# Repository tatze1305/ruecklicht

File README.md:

# Project Title

Look in PDF/schematic and PDF/pcb!!!

---

## 3D Preview

### Rücklicht – Back View

### Rücklicht – Front View

---

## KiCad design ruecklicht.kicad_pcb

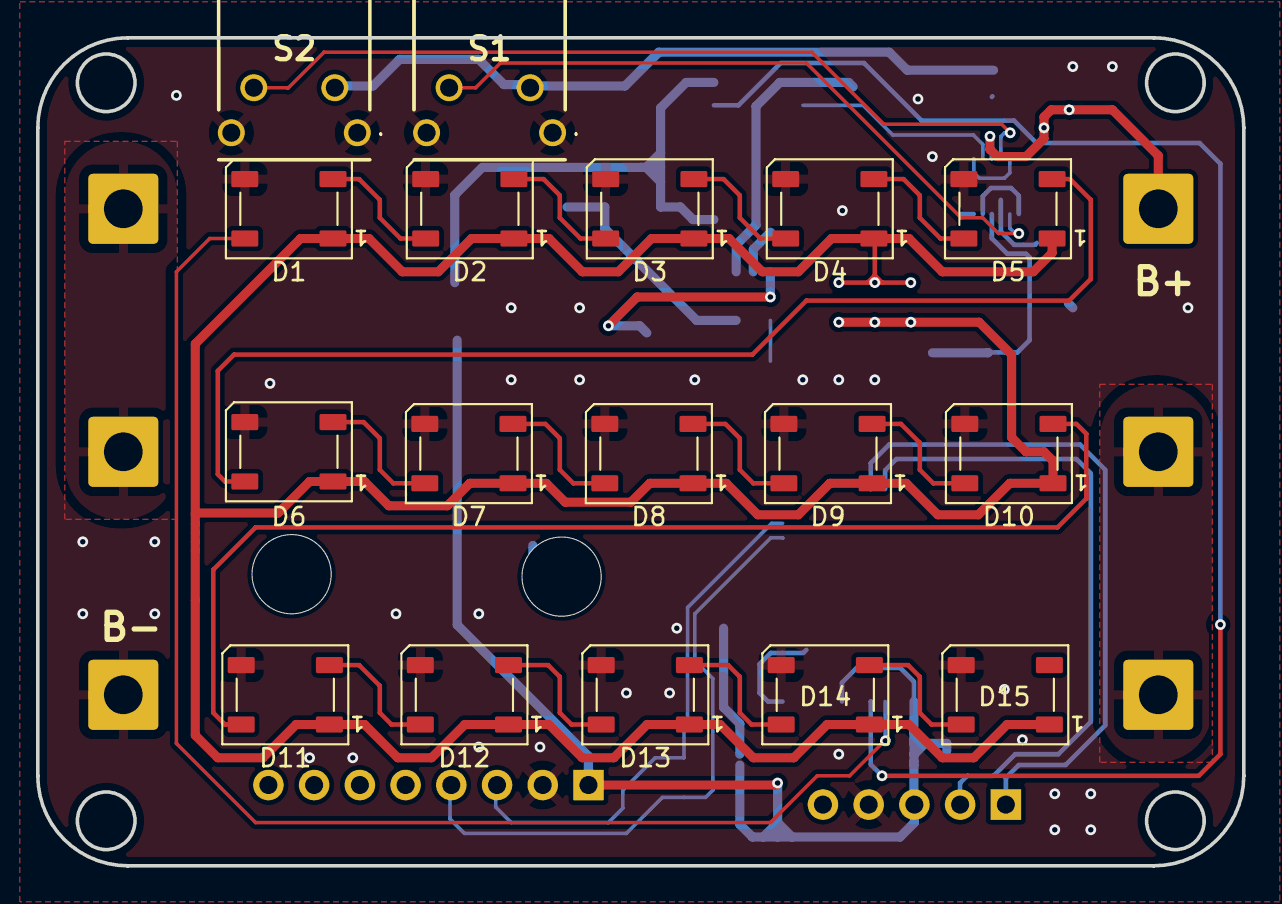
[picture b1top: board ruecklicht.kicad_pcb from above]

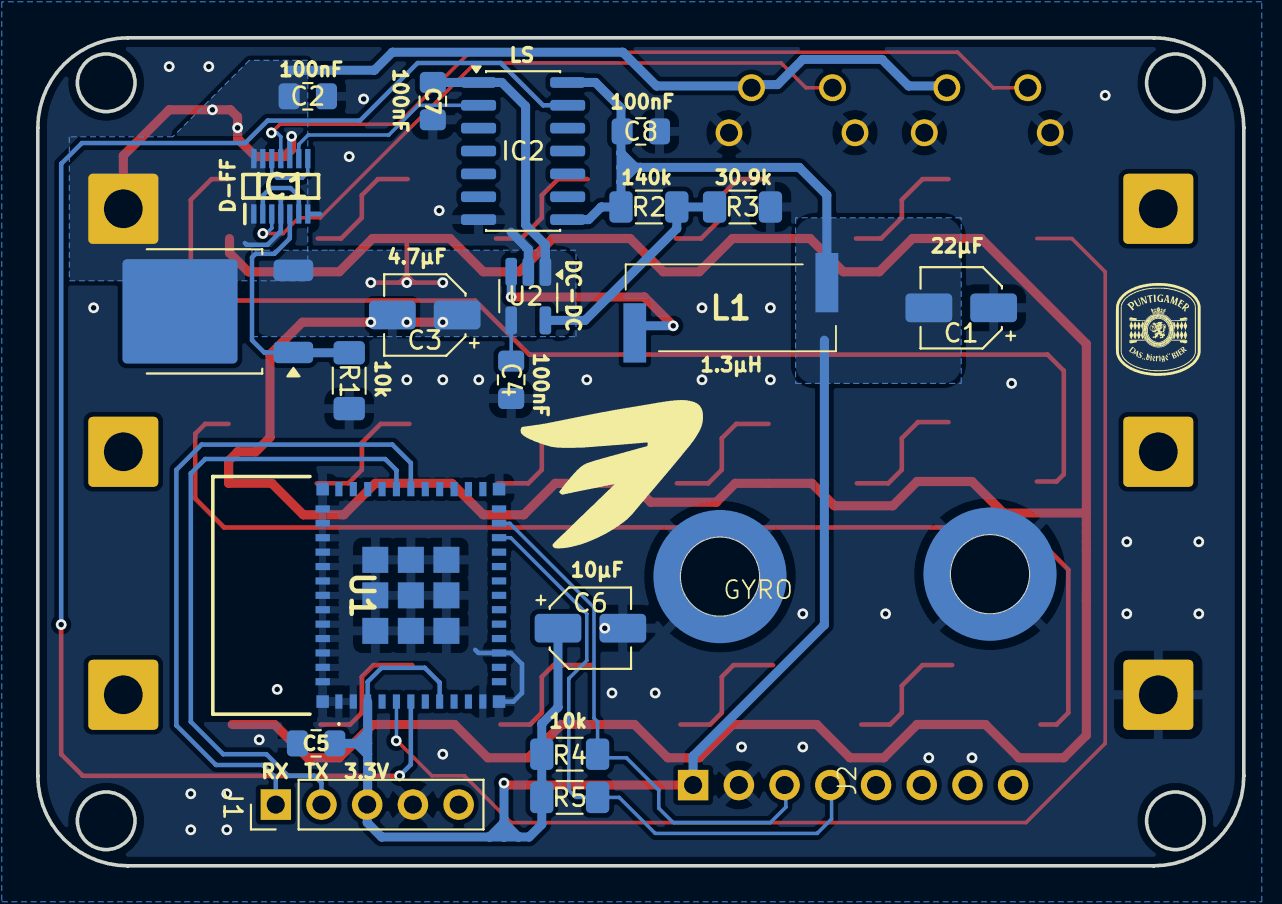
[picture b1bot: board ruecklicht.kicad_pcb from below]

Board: 2 copper layers, 67.0 x 46.0 mm, 44 parts (21 on the bottom side), 34 nets.

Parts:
B1+1, B1-1, B2+1, B2-1, B3+1, B3-1: Conn_01x01_Pin; SolderWire-1.5sqmm_1x01_D1.7mm_OD3.9mm
C1: 22µF; CP_Elec_4x5.4
C2, C4, C5, C7, C8: 100nF; C_0805_2012Metric_Pad1.18x1.45mm_HandSolder
C3: 4.7µF; CP_Elec_4x5.4
C6: 10µF; CP_Elec_4x5.4
D1, D2, D3, D4, D5, D6, D7, D8, D9, D10, D11, D12, D13, D14, D15: WS2812B; LED_WS2812B_PLCC4_5.0x5.0mm_P3.2mm
IC1: SN74HCS74QDYYRQ1; SOP50P326X110-14N
IC2: TXS0104EDG4; SOIC-14_3.9x8.7mm_P1.27mm
J1: Conn_01x05_Pin; PinHeader_1x05_P2.54mm_Vertical
J2: Conn_01x08_Pin; mpu6050-self
L1: 1.3u; 4310LC132KEC
Q1: NMOS; mosfet
R1: 10k; R_1206_3216Metric_Pad1.30x1.75mm_HandSolder
R2: 140k; R_1206_3216Metric_Pad1.30x1.75mm_HandSolder
R3: 30.9k; R_1206_3216Metric_Pad1.30x1.75mm_HandSolder
R4, R5: R_Small; R_1206_3216Metric_Pad1.30x1.75mm_HandSolder
S1, S2: 431256083716
U1: ESP32-C3-MINI-1-H4X; ESP32C3MINI1H4X
U2: MP2128DT-LF-P; SOT-23-5_HandSoldering

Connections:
+3.3V: C1.2, C5.1, C6.1, C8.2, IC2.8 (OE), IC2.14 (VCCB), J1.3, J2.1, L1.1, R2.1, R4.1, R5.1, U1.3 (3V3), U1.8 (EN)
/4.5_GEN: C3.1, C4.1, C7.2, D1.1 (VDD), D2.1 (VDD), D3.1 (VDD), D4.1 (VDD), D5.1 (VDD), D6.1 (VDD), D7.1 (VDD), D8.1 (VDD), D9.1 (VDD), D10.1 (VDD), D11.1 (VDD), D12.1 (VDD), D13.1 (VDD), D14.1 (VDD), D15.1 (VDD), IC2.1 (VCCA), Q1.3 (S), U2.1 (EN), U2.4 (IN)
/B+: B1+1.1, C2.2, IC1.1 (1~CLR), IC1.4 (1~PRE), IC1.10 (2~PRE), IC1.13 (2~CLR), IC1.14 (VCC), Q1.1 (D), S1.2 (COM), S2.2 (COM)
/BT_EN_3.3: IC2.13 (B1), U1.6 (IO3)
/BT_EN_4.5: IC1.9 (2Q), IC2.2 (A1)
/D+: D1.4 (DIN), U1.5 (IO2)
/ESP32/RX: J1.1, U1.30 (RXD0)
/ESP32/TX: J1.2, U1.31 (TXD0)
/SCL: J2.3, R4.2, U1.23 (IO9)
/SDA: J2.4, R5.2, U1.22 (IO8)
/leds/D1: D5.2 (DOUT), D6.4 (DIN)
/leds/D2: D10.2 (DOUT), D11.4 (DIN)
/switches/BT_EN_Button/NO: IC1.11 (2CLK), S2.3 (NO)
/switches/EN_Button/NO: IC1.3 (1CLK), S1.3 (NO)
/switches/Q1: IC1.5 (1Q), Q1.2 (G), R1.1
/switches/d-ff/q-inv: IC1.2 (1D), IC1.6 (1~Q)
/switches/d-ff/q-inv2: IC1.8 (2~Q), IC1.12 (2D)
GND: B3-1.1, C1.1, C2.1, C3.2, C4.2, C5.2, C6.2, C7.1, C8.1, D1.3 (VSS), D2.3 (VSS), D3.3 (VSS), D4.3 (VSS), D5.3 (VSS), D6.3 (VSS), D7.3 (VSS), D8.3 (VSS), D9.3 (VSS), D10.3 (VSS), D11.3 (VSS), D12.3 (VSS), D13.3 (VSS), D14.3 (VSS), D15.3 (VSS), IC1.7 (GND), IC2.7 (GND), J1.4, J2.2, R1.2, R3.2, S1.1 (GND_1), S1.4 (GND_2), S2.1 (GND_1), S2.4 (GND_2), U1.1 (GND_1), U1.2 (GND_2), U1.11 (GND_3), U1.14 (GND_4), U1.36 (GND_5), U1.37 (GND_6), U1.38 (GND_7), U1.39 (GND_8), U1.40 (GND_9), U1.41 (GND_10), U1.42 (GND_11), U1.43 (GND_12), U1.44 (GND_13), U1.45 (GND_14), U1.46 (GND_15), U1.47 (GND_16), U1.48 (GND_17), U1.49 (GND_18), U1.50 (GND_19), U1.51 (GND_20), U1.52 (GND_21), U1.53 (GND_22), U1.54 (GND_23), U1.55 (GND_24), U1.56 (GND_25), U1.57 (GND_26), U1.58 (GND_27), U1.59 (GND_28), U1.60 (GND_29), U1.61 (GND_30), U2.2 (GND)
unnamed: B1-1.1, B2+1.1
unnamed: B2-1.1, B3+1.1
unnamed: D1.2 (DOUT), D2.4 (DIN)
unnamed: D2.2 (DOUT), D3.4 (DIN)
unnamed: D3.2 (DOUT), D4.4 (DIN)
unnamed: D4.2 (DOUT), D5.4 (DIN)
unnamed: D6.2 (DOUT), D7.4 (DIN)
unnamed: D7.2 (DOUT), D8.4 (DIN)
unnamed: D8.2 (DOUT), D9.4 (DIN)
unnamed: D9.2 (DOUT), D10.4 (DIN)
unnamed: D11.2 (DOUT), D12.4 (DIN)
unnamed: D12.2 (DOUT), D13.4 (DIN)
unnamed: D13.2 (DOUT), D14.4 (DIN)
unnamed: D14.2 (DOUT), D15.4 (DIN)
unnamed: R2.2, R3.1, U2.5 (FB)
unnamed: L1.2, U2.3 (SW)

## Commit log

2025-11-10 init commit
2025-11-10 stand 15:32
2025-11-10 stand ende 10.11.2025
2025-11-15 15.11.2025 15:12:00
2025-11-15 15.11.2025 16:38
2025-11-15 15.11.2025 16:51
2025-11-16 16.11.2025 13:36 -> Schematic Finished (possible)
2025-11-16 16.11.2025 16:28 -> began with pcb
2025-11-16 Finished Rev.1
2025-11-17 stand before gyro change
2025-11-17 Finished Rev.1 -> possible order
2025-11-24 stand 14:40 24.11.2025
